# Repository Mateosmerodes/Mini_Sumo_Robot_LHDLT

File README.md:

# Mini_Sumo_Robot_LHDLT
Repositorio de informacion y código proyecto minisumo

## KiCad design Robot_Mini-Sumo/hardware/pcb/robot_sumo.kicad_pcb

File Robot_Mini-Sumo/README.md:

# 🍺 Robot Mini-Sumo · Hombres de las Tabernas

Robot mini-sumo autónomo (10 × 10 cm, < 500 g) para **Tecnología Eléctrica**, Grado en Robótica (USC), 2.ª edición. Compite según el reglamento **OSHWDem Mini Sumo rev. 7**.

**Equipo:** Mateo Esmerodes Rodríguez · Paulo Bouza García · Mario Costoya Mera

## Concepto

Rampa (cuña) clásica, **tracción 4WD** con 4 N20, una **ESP32-S3-DevKitC-1 enchufada** sobre una **PCB propia que es también el chasis**, 6 sensores ToF para encontrar al rival, 4 de línea y arranque por IR (RC5).

## Documentación

| Doc | Contenido | Estado |
|---|---|---|
| [00 · Requisitos y reglamento](docs/00-Requisitos-y-reglamento.md) | Lo que obliga al diseño | ✅ |
| [01 · Selección de componentes](docs/01-Seleccion-de-componentes.md) | Qué pieza y por qué | ✅ borrador |
| [02 · Arquitectura eléctrica](docs/02-Arquitectura-electrica.md) | Alimentación, interconexión, pinout | ✅ borrador |
| [03 · Disposición mecánica y 3D](docs/03-Disposicion-mecanica.md) | Piezas, niveles, masas, montaje, impresión | ✅ borrador |
| [04 · ESP32-S3-DevKitC-1](docs/04-ESP32-DevKitC-1.md) | Cambio a DevKit enchufable: montaje, alimentación, pinout, rutado | ✅ borrador |
| 05 · Diseño de la PCB | Esquemático ✅, colocación v1.1 ✅, ERC/DRC en KiCad 10 ⏳, rutado ⏳ | 🟡 |
| 06 · Lista de compra | AliExpress + LCSC/JLC | ⏳ |
| 07 · Costes | Desglose para el informe | ⏳ |
| Informe final | 6 páginas | ⏳ |
| [📝 Ficha técnica](docs/Ficha-tecnica.md) | Respuestas a la ficha de la competición, con los cálculos (consumo, autonomía, corrientes) | ✅ |
| [📊 Consumos y cálculos](docs/Informe-consumos-y-calculos.md) | Pieza a pieza con fuentes oficiales; cálculos de batería, motores, potencia, autonomía y señales (`hardware/calculos/`) | ✅ |
| [📋 Informe de progreso 06/10/2026](docs/Informe-progreso-2026-10-06.md) | Resumen para el equipo: proceso, compra, útiles, problemas | ✅ |

## Estructura

```
docs/                   Documentación (también es una bóveda de Obsidian)
hardware/geometria.py   Parámetros mecánicos compartidos (PCB + 3D)
hardware/generar_todo.sh  Regenera PCB, 3D, STL/STEP e imágenes
hardware/pcb/           Proyecto KiCad (scripts/design.py = circuito)
hardware/mecanica/cad/  Modelo 3D paramétrico (FreeCAD) y renderizador
hardware/mecanica/step/ Exportaciones STEP (Onshape/FreeCAD)
hardware/mecanica/stl/  Piezas listas para imprimir
firmware/               Código del ESP32-S3 (Arduino/PlatformIO; pines en docs/04)
media/fotos/            Fotos del proceso
informe/                Informe de entrega
```

## Herramientas (Linux)

```bash
sudo pacman -S --needed kicad kicad-library freecad
```

Opcional, para exportar la PCB a 3D con todos los componentes (~5 GB):

```bash
sudo pacman -S --needed kicad-library-3d
```

Licencias: hardware **CERN-OHL-S v2**, software **MIT**.

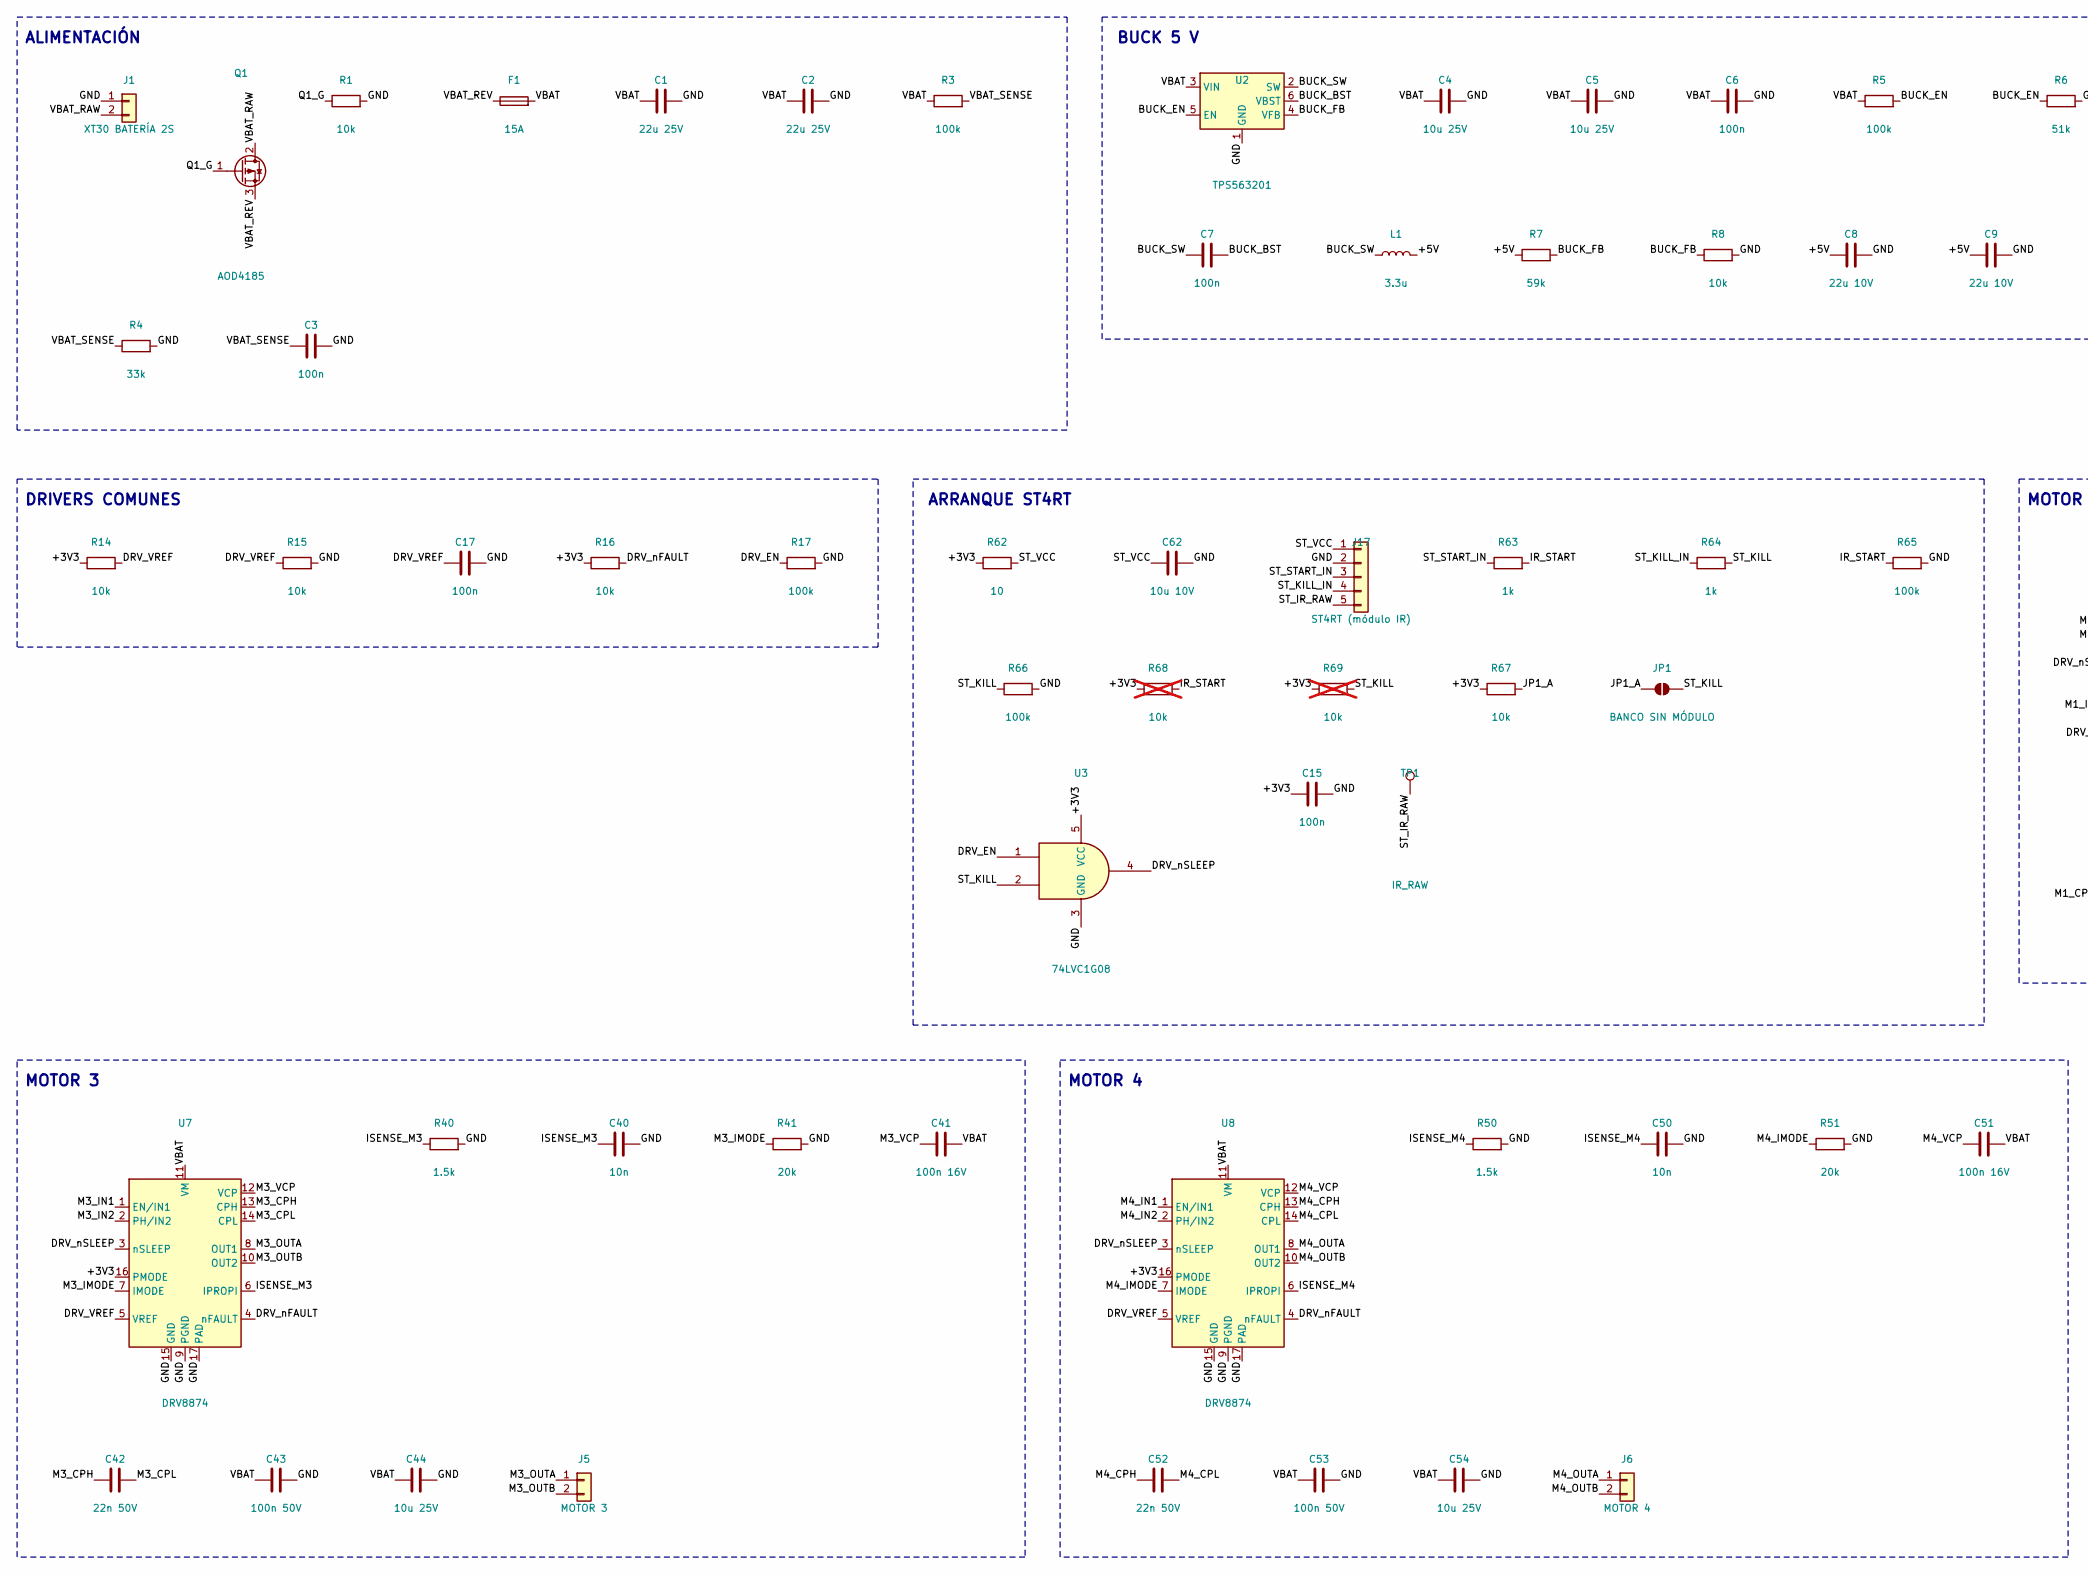
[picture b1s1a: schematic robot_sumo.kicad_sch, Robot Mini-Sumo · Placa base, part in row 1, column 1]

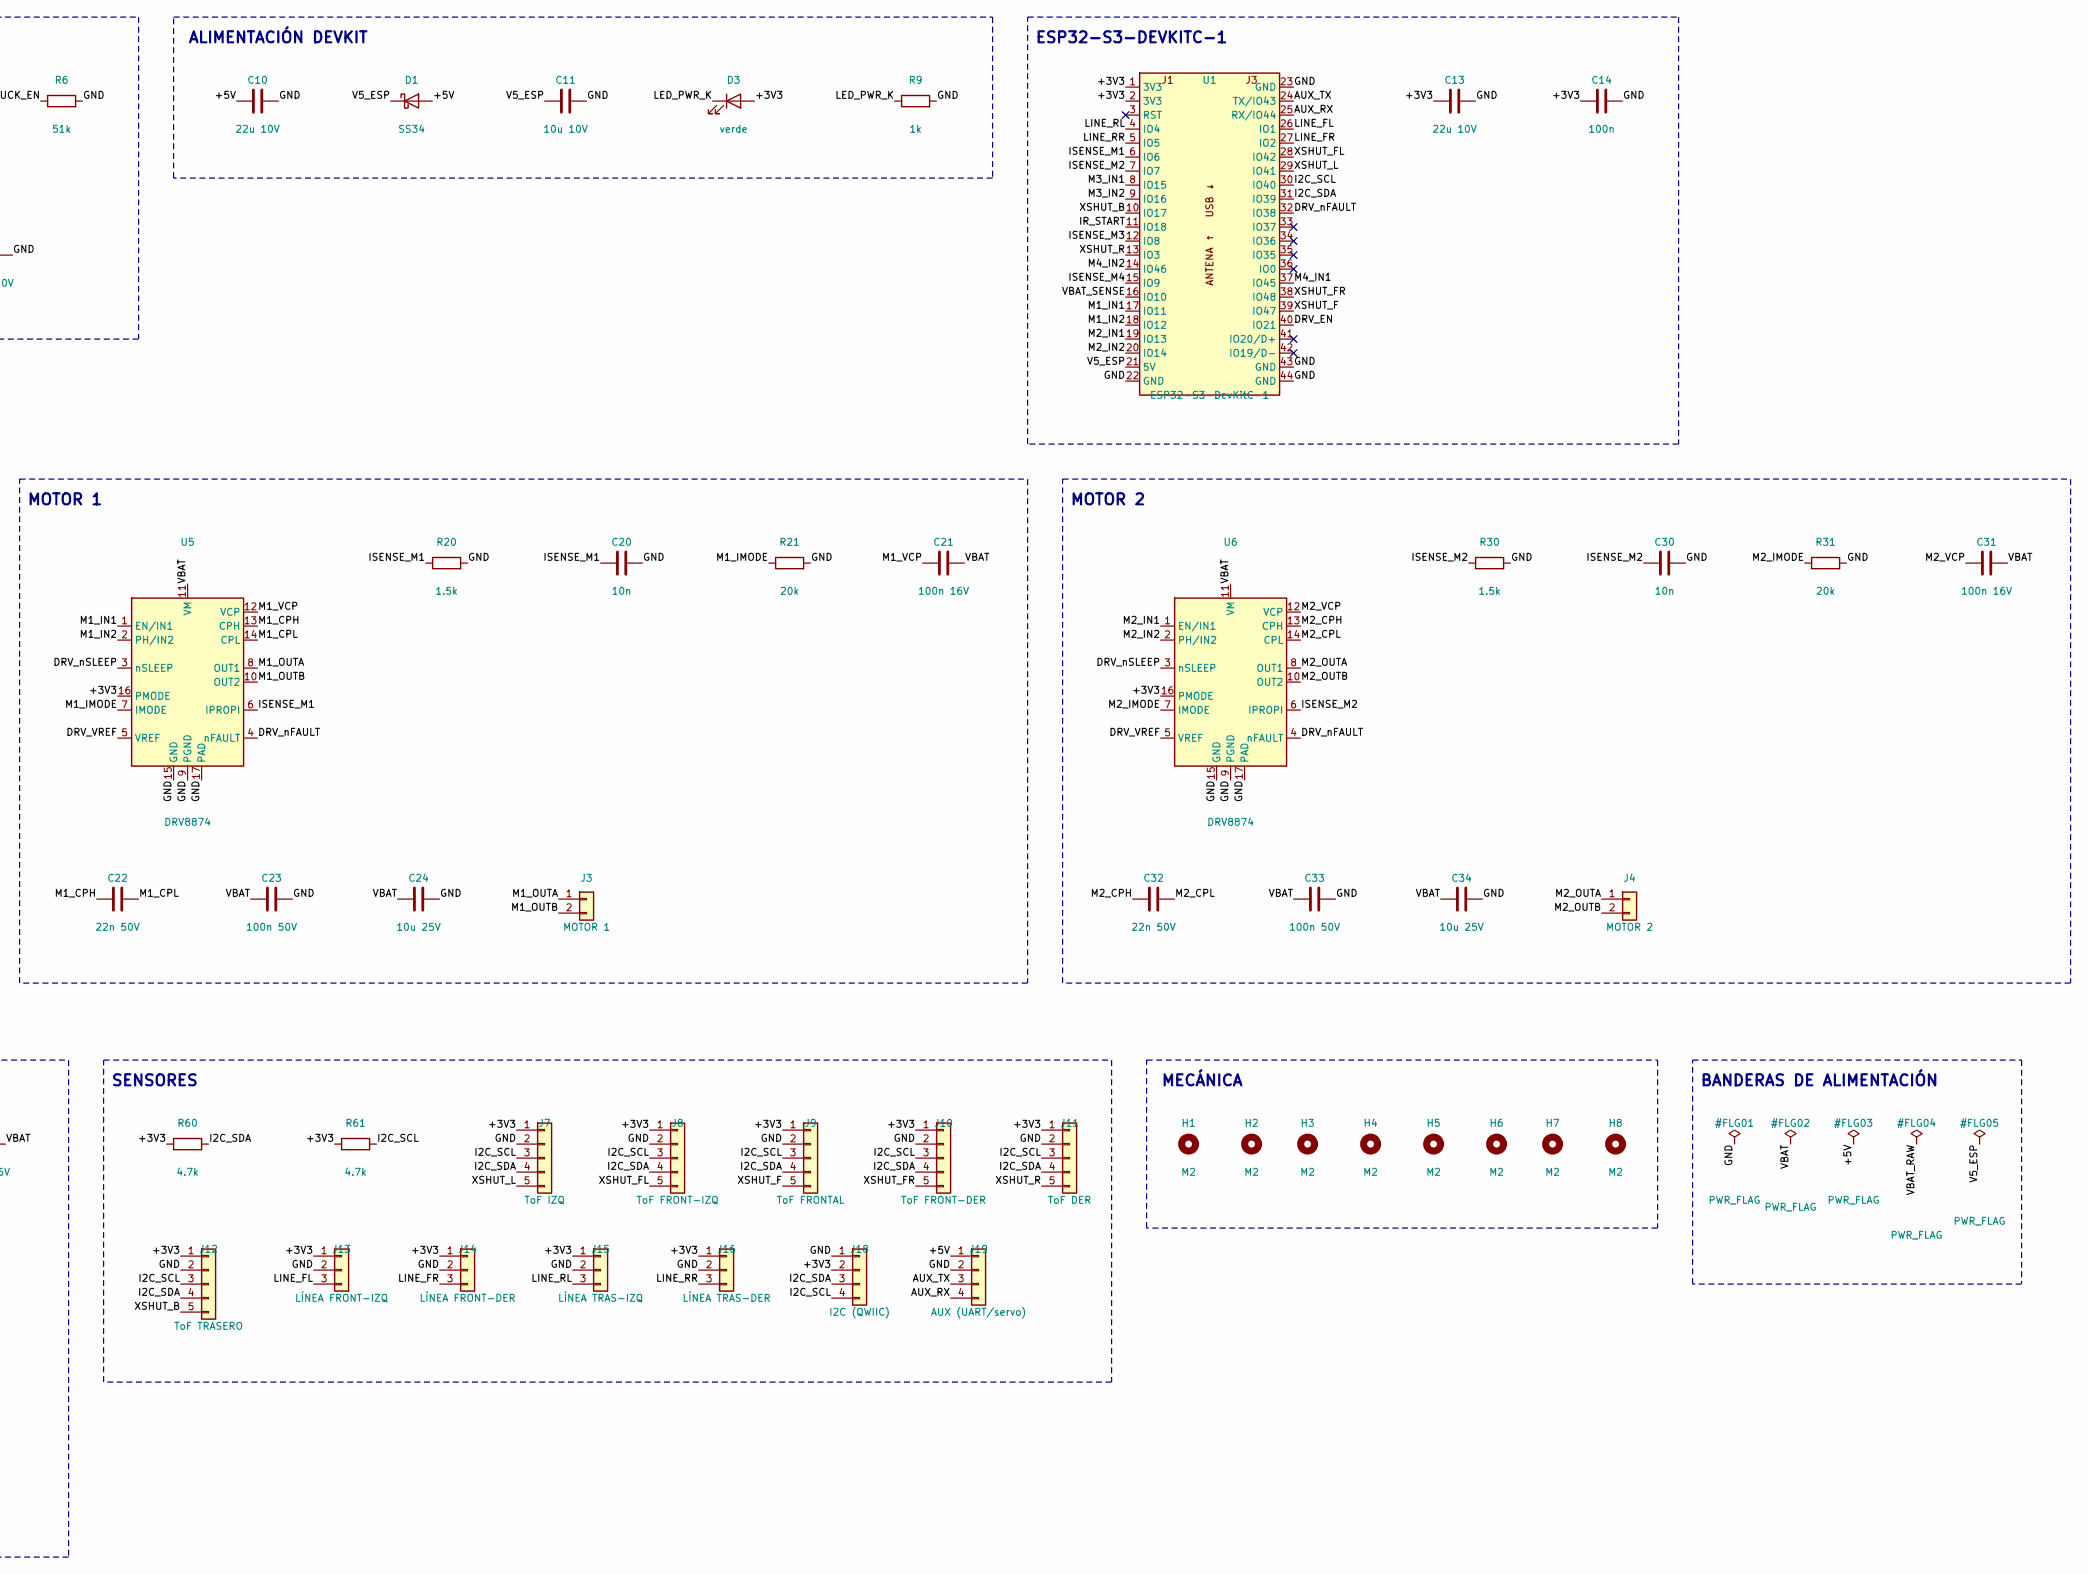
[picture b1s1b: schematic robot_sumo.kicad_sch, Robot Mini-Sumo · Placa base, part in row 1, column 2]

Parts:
C1, C2: 22u 25V; C_1206_3216Metric
C3, C6, C7, C14, C15, C17: 100n; C_0603_1608Metric
C4, C5, C24, C34, C44, C54: 10u 25V; C_1206_3216Metric
C8, C9, C10, C13: 22u 10V; C_1206_3216Metric
C11, C62: 10u 10V; C_0805_2012Metric
C20, C30, C40, C50: 10n; C_0603_1608Metric
C21, C31, C41, C51: 100n 16V; C_0402_1005Metric
C22, C32, C42, C52: 22n 50V; C_0402_1005Metric
C23, C33, C43, C53: 100n 50V; C_0603_1608Metric
D1: SS34; D_SMA
D3: verde; LED_0603_1608Metric
F1: 15A; Fuse_Littelfuse-NANO2-451_453; MPN Littelfuse NANO2 451/453, 15 A rápido (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
H1, H2, H3, H4, H5, H6, H7, H8: M2; MountingHole_2.2mm_M2
J1: XT30 BATERÍA 2S; AMASS_XT30UPB-M_1x02_P5.0mm_Vertical; MPN AMASS XT30UPB-M (macho, vertical PCB)
J3: MOTOR 1; SolderWire-0.5sqmm_1x02_P4.6mm_D0.9mm_OD2.1mm; MPN Cable del motor soldado (entra por abaj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
J4: MOTOR 2; SolderWire-0.5sqmm_1x02_P4.6mm_D0.9mm_OD2.1mm; MPN Cable del motor soldado (entra por abaj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
J5: MOTOR 3; SolderWire-0.5sqmm_1x02_P4.6mm_D0.9mm_OD2.1mm; MPN Cable del motor soldado (entra por abaj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
J6: MOTOR 4; SolderWire-0.5sqmm_1x02_P4.6mm_D0.9mm_OD2.1mm; MPN Cable del motor soldado (entra por abaj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
J7: ToF IZQ; JST_SH_BM05B-SRSS-TB_1x05-1MP_P1.00mm_Vertical; MPN JST SH 5P SMD vertical (BM05B-SRSS-TB)
J8: ToF FRONT-IZQ; JST_SH_BM05B-SRSS-TB_1x05-1MP_P1.00mm_Vertical; MPN JST SH 5P SMD vertical (BM05B-SRSS-TB)
J9: ToF FRONTAL; JST_SH_BM05B-SRSS-TB_1x05-1MP_P1.00mm_Vertical; MPN JST SH 5P SMD vertical (BM05B-SRSS-TB)
J10: ToF FRONT-DER; JST_SH_BM05B-SRSS-TB_1x05-1MP_P1.00mm_Vertical; MPN JST SH 5P SMD vertical (BM05B-SRSS-TB)
J11: ToF DER; JST_SH_BM05B-SRSS-TB_1x05-1MP_P1.00mm_Vertical; MPN JST SH 5P SMD vertical (BM05B-SRSS-TB)
J12: ToF TRASERO; JST_SH_BM05B-SRSS-TB_1x05-1MP_P1.00mm_Vertical; MPN JST SH 5P SMD vertical (BM05B-SRSS-TB)
J13: LÍNEA FRONT-IZQ; JST_SH_BM03B-SRSS-TB_1x03-1MP_P1.00mm_Vertical; MPN JST SH 3P SMD vertical (BM03B-SRSS-TB)
J14: LÍNEA FRONT-DER; JST_SH_BM03B-SRSS-TB_1x03-1MP_P1.00mm_Vertical; MPN JST SH 3P SMD vertical (BM03B-SRSS-TB)
J15: LÍNEA TRAS-IZQ; JST_SH_BM03B-SRSS-TB_1x03-1MP_P1.00mm_Vertical; MPN JST SH 3P SMD vertical (BM03B-SRSS-TB)
J16: LÍNEA TRAS-DER; JST_SH_BM03B-SRSS-TB_1x03-1MP_P1.00mm_Vertical; MPN JST SH 3P SMD vertical (BM03B-SRSS-TB)
J17: ST4RT (módulo IR); JST_SH_BM05B-SRSS-TB_1x05-1MP_P1.00mm_Vertical; MPN JST SH 5P SMD vertical (BM05B-SRSS-TB) 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
J18: I2C (QWIIC); JST_SH_BM04B-SRSS-TB_1x04-1MP_P1.00mm_Vertical; MPN JST SH 4P SMD vertical (BM04B-SRSS-TB)
J19: AUX (UART/servo); JST_SH_BM04B-SRSS-TB_1x04-1MP_P1.00mm_Vertical; MPN JST SH 4P SMD vertical (BM04B-SRSS-TB)
JP1: BANCO SIN MÓDULO; SolderJumper-2_P1.3mm_Open_RoundedPad1.0x1.5mm; MPN Puente de soldadura: cerrado = KILL a 1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
L1: 3.3u; L_Bourns-SRN4018; MPN SRN4018-3R3M (3,3 µH, Isat ≥ 2,5 A)
Q1: AOD4185; TO-252-2; MPN AOD4185 (-40 V, -40 A, 15 mΩ)
R1, R8, R14, R15, R16, R67: 10k; R_0603_1608Metric
R3, R5, R17, R65, R66: 100k; R_0603_1608Metric
R4: 33k; R_0603_1608Metric
R6: 51k; R_0603_1608Metric
R7: 59k; R_0603_1608Metric
R9, R63, R64: 1k; R_0603_1608Metric
R20, R30, R40, R50: 1.5k; R_0603_1608Metric
R21, R31, R41, R51: 20k; R_0603_1608Metric
R60, R61: 4.7k; R_0603_1608Metric
R62: 10; R_0603_1608Metric
R68: 10k; R_0603_1608Metric; MPN DNP: solo si S es de drenador abierto; not fitted
R69: 10k; R_0603_1608Metric; MPN DNP: solo si K es de drenador abierto; not fitted
TP1: IR_RAW; TestPoint_Pad_D1.0mm; MPN Punto de prueba (salida IR en bruto del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
U1: ESP32-S3-DevKitC-1; ESP32-S3-DevKitC-1_Zocalo; MPN ESP32-S3-DevKitC-1 (cualquier variante: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
U2: TPS563201; SOT-23-6; MPN TPS563201DDCR
U3: 74LVC1G08; SOT-23-5; MPN SN74LVC1G08DBVR
U5, U6, U7, U8: DRV8874; HTSSOP-16-1EP_4.4x5mm_P0.65mm_EP3.4x5mm_Mask2.46x2.31mm; MPN DRV8874PWPR

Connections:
+3V3: C13.1, C14.1, C15.1, D3.2 (A), J7.1, J8.1, J9.1, J10.1, J11.1, J12.1, J13.1, J14.1, J15.1, J16.1, J18.2, R14.1, R16.1, R60.1, R61.1, R62.1, R67.1, R68.1, R69.1, U1.1 (3V3), U1.2 (3V3), U3.5 (VCC), U5.16 (PMODE), U6.16 (PMODE), U7.16 (PMODE), U8.16 (PMODE)
+5V: C8.1, C9.1, C10.1, D1.2 (A), J19.1, L1.2, R7.1
AUX_RX: J19.4, U1.25 (RX/IO44)
AUX_TX: J19.3, U1.24 (TX/IO43)
BUCK_BST: C7.2, U2.6 (VBST)
BUCK_EN: R5.2, R6.1, U2.5 (EN)
BUCK_FB: R7.2, R8.1, U2.4 (VFB)
BUCK_SW: C7.1, L1.1, U2.2 (SW)
DRV_EN: R17.1, U1.40 (IO21), U3.1
DRV_VREF: C17.1, R14.2, R15.1, U5.5 (VREF), U6.5 (VREF), U7.5 (VREF), U8.5 (VREF)
DRV_nFAULT: R16.2, U1.32 (IO38), U5.4 (nFAULT), U6.4 (nFAULT), U7.4 (nFAULT), U8.4 (nFAULT)
DRV_nSLEEP: U3.4, U5.3 (nSLEEP), U6.3 (nSLEEP), U7.3 (nSLEEP), U8.3 (nSLEEP)
GND: C1.2, C2.2, C3.2, C4.2, C5.2, C6.2, C8.2, C9.2, C10.2, C11.2, C13.2, C14.2, C15.2, C17.2, C20.2, C23.2, C24.2, C30.2, C33.2, C34.2, C40.2, C43.2, C44.2, C50.2, C53.2, C54.2, C62.2, J1.1, J7.2, J8.2, J9.2, J10.2, J11.2, J12.2, J13.2, J14.2, J15.2, J16.2, J17.2, J18.1, J19.2, R1.2, R4.2, R6.2, R8.2, R9.2, R15.2, R17.2, R20.2, R21.2, R30.2, R31.2, R40.2, R41.2, R50.2, R51.2, R65.2, R66.2, U1.22 (GND), U1.23 (GND), U1.43 (GND), U1.44 (GND), U2.1 (GND), U3.3 (GND), U5.9 (PGND), U5.15 (GND), U5.17 (PAD), U6.9 (PGND), U6.15 (GND), U6.17 (PAD), U7.9 (PGND), U7.15 (GND), U7.17 (PAD), U8.9 (PGND), U8.15 (GND), U8.17 (PAD)
I2C_SCL: J7.3, J8.3, J9.3, J10.3, J11.3, J12.3, J18.4, R61.2, U1.30 (IO40)
I2C_SDA: J7.4, J8.4, J9.4, J10.4, J11.4, J12.4, J18.3, R60.2, U1.31 (IO39)
IR_START: R63.2, R65.1, R68.2, U1.11 (IO18)
ISENSE_M1: C20.1, R20.1, U1.6 (IO6), U5.6 (IPROPI)
ISENSE_M2: C30.1, R30.1, U1.7 (IO7), U6.6 (IPROPI)
ISENSE_M3: C40.1, R40.1, U1.12 (IO8), U7.6 (IPROPI)
ISENSE_M4: C50.1, R50.1, U1.15 (IO9), U8.6 (IPROPI)
JP1_A: JP1.1 (A), R67.2
LED_PWR_K: D3.1 (K), R9.1
LINE_FL: J13.3, U1.26 (IO1)
LINE_FR: J14.3, U1.27 (IO2)
LINE_RL: J15.3, U1.4 (IO4)
LINE_RR: J16.3, U1.5 (IO5)
M1_CPH: C22.1, U5.13 (CPH)
M1_CPL: C22.2, U5.14 (CPL)
M1_IMODE: R21.1, U5.7 (IMODE)
M1_IN1: U1.17 (IO11), U5.1 (EN/IN1)
M1_IN2: U1.18 (IO12), U5.2 (PH/IN2)
M1_OUTA: J3.1, U5.8 (OUT1)
M1_OUTB: J3.2, U5.10 (OUT2)
M1_VCP: C21.1, U5.12 (VCP)
M2_CPH: C32.1, U6.13 (CPH)
M2_CPL: C32.2, U6.14 (CPL)
M2_IMODE: R31.1, U6.7 (IMODE)
M2_IN1: U1.19 (IO13), U6.1 (EN/IN1)
M2_IN2: U1.20 (IO14), U6.2 (PH/IN2)
M2_OUTA: J4.1, U6.8 (OUT1)
M2_OUTB: J4.2, U6.10 (OUT2)
M2_VCP: C31.1, U6.12 (VCP)
M3_CPH: C42.1, U7.13 (CPH)
M3_CPL: C42.2, U7.14 (CPL)
M3_IMODE: R41.1, U7.7 (IMODE)
M3_IN1: U1.8 (IO15), U7.1 (EN/IN1)
M3_IN2: U1.9 (IO16), U7.2 (PH/IN2)
M3_OUTA: J5.1, U7.8 (OUT1)
M3_OUTB: J5.2, U7.10 (OUT2)
M3_VCP: C41.1, U7.12 (VCP)
M4_CPH: C52.1, U8.13 (CPH)
M4_CPL: C52.2, U8.14 (CPL)
M4_IMODE: R51.1, U8.7 (IMODE)
M4_IN1: U1.37 (IO45), U8.1 (EN/IN1)
M4_IN2: U1.14 (IO46), U8.2 (PH/IN2)
M4_OUTA: J6.1, U8.8 (OUT1)
M4_OUTB: J6.2, U8.10 (OUT2)
M4_VCP: C51.1, U8.12 (VCP)
Q1_G: Q1.1 (G), R1.1
ST_IR_RAW: J17.5, TP1.1
ST_KILL: JP1.2 (B), R64.2, R66.1, R69.2, U3.2
ST_KILL_IN: J17.4, R64.1
ST_START_IN: J17.3, R63.1
ST_VCC: C62.1, J17.1, R62.2
V5_ESP: C11.1, D1.1 (K), U1.21 (5V)
VBAT: C1.1, C2.1, C4.1, C5.1, C6.1, C21.2, C23.1, C24.1, C31.2, C33.1, C34.1, C41.2, C43.1, C44.1, C51.2, C53.1, C54.1, F1.2, R3.1, R5.1, U2.3 (VIN), U5.11 (VM), U6.11 (VM), U7.11 (VM), U8.11 (VM)
VBAT_RAW: J1.2, Q1.2 (D)
VBAT_REV: F1.1, Q1.3 (S)
VBAT_SENSE: C3.1, R3.2, R4.1, U1.16 (IO10)
XSHUT_B: J12.5, U1.10 (IO17)
XSHUT_F: J9.5, U1.39 (IO47)
XSHUT_FL: J8.5, U1.28 (IO42)
XSHUT_FR: J10.5, U1.38 (IO48)
XSHUT_L: J7.5, U1.29 (IO41)
XSHUT_R: J11.5, U1.13 (IO3)

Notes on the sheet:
ALIMENTACIÓN
BUCK 5 V
ALIMENTACIÓN DEVKIT
ESP32-S3-DEVKITC-1
DRIVERS COMUNES
ARRANQUE ST4RT
MOTOR 1
MOTOR 2
MOTOR 3
MOTOR 4
SENSORES
MECÁNICA
BANDERAS DE ALIMENTACIÓN

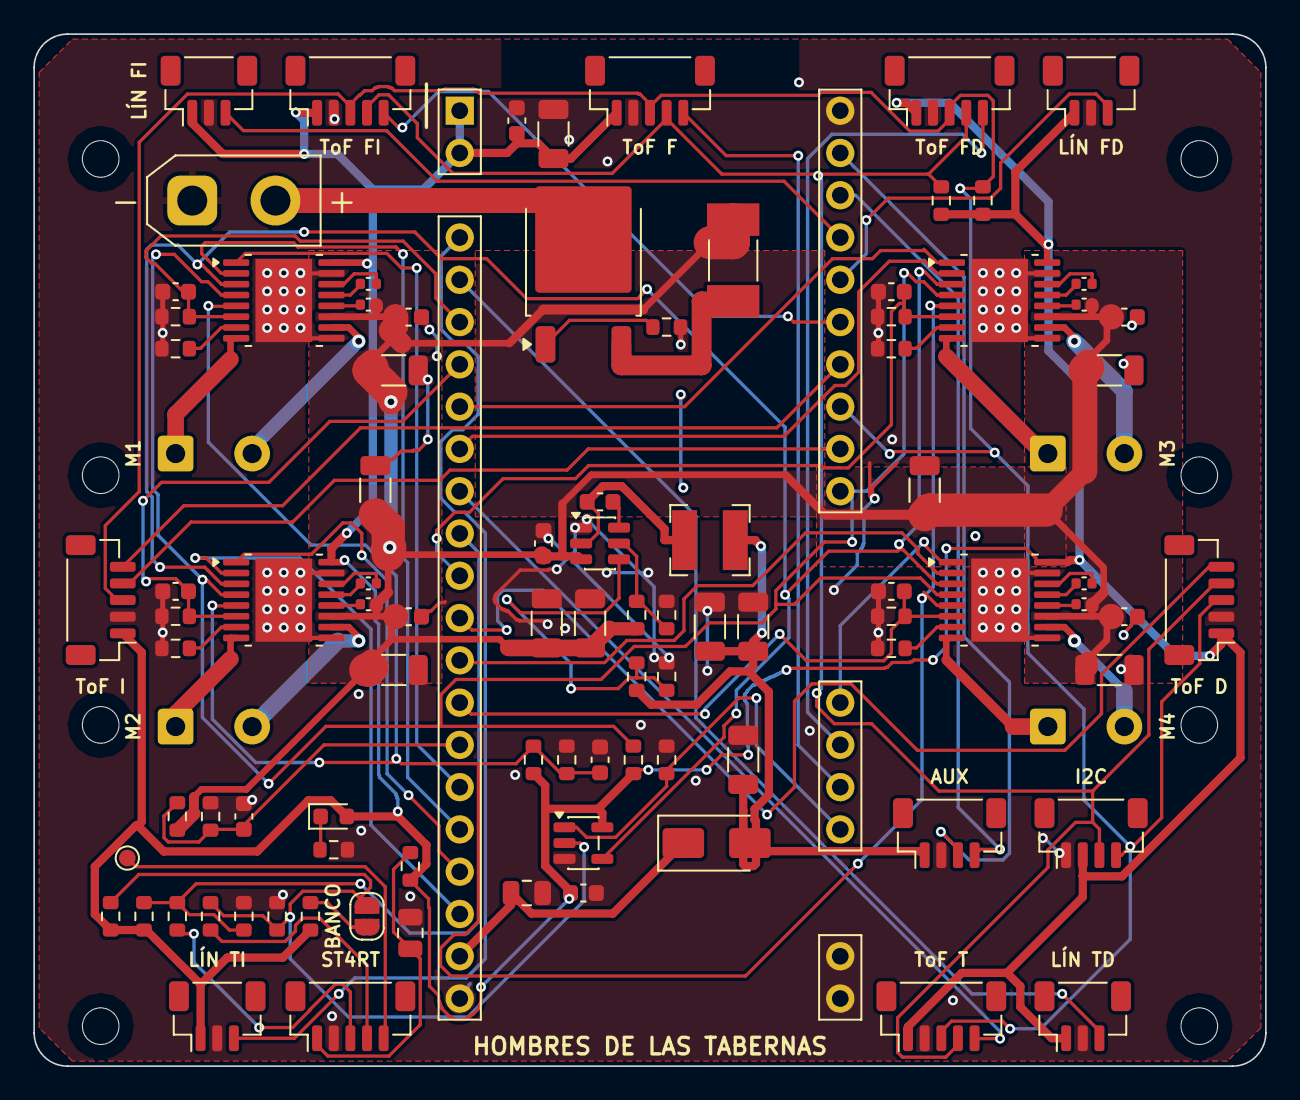
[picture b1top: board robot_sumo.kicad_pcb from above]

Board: 2 copper layers, 74.0 x 62.0 mm, 106 parts (0 on the bottom side), 75 nets.

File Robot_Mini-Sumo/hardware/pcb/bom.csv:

Comment,Designator,Footprint,LCSC,MPN,Cantidad
22u 25V,"C1,C2",C_1206_3216Metric,,,2
100n,"C3,C6,C7,C14,C15,C17",C_0603_1608Metric,,,6
10u 25V,"C4,C5,C24,C34,C44,C54",C_1206_3216Metric,,,6
22u 10V,"C8,C9,C10,C13",C_1206_3216Metric,,,4
10u 10V,"C11,C62",C_0805_2012Metric,,,2
10n,"C20,C30,C40,C50",C_0603_1608Metric,,,4
100n 16V,"C21,C31,C41,C51",C_0603_1608Metric,,,4
22n 50V,"C22,C32,C42,C52",C_0603_1608Metric,,,4
100n 50V,"C23,C33,C43,C53",C_0603_1608Metric,,,4
SS34,D1,D_SMA,,,1
verde,D3,LED_0603_1608Metric,,,1
15A,F1,Fuse_Littelfuse-NANO2-451_453,,"Littelfuse NANO2 451/453, 15 A rápido (p. ej. 0451015.MRL; verificar stock)",1
XT30 BATERÍA 2S,J1,AMASS_XT30UPB-M_1x02_P5.0mm_Vertical,,"AMASS XT30UPB-M (macho, vertical PCB)",1
MOTOR 1,J3,SolderWire-0.5sqmm_1x02_P4.6mm_D0.9mm_OD2.1mm,,Cable del motor soldado (entra por abajo),1
MOTOR 2,J4,SolderWire-0.5sqmm_1x02_P4.6mm_D0.9mm_OD2.1mm,,Cable del motor soldado (entra por abajo),1
MOTOR 3,J5,SolderWire-0.5sqmm_1x02_P4.6mm_D0.9mm_OD2.1mm,,Cable del motor soldado (entra por abajo),1
MOTOR 4,J6,SolderWire-0.5sqmm_1x02_P4.6mm_D0.9mm_OD2.1mm,,Cable del motor soldado (entra por abajo),1
ToF IZQ,J7,JST_SH_BM05B-SRSS-TB_1x05-1MP_P1.00mm_Vertical,,JST SH 5P SMD vertical (BM05B-SRSS-TB),1
ToF FRONT-IZQ,J8,JST_SH_BM05B-SRSS-TB_1x05-1MP_P1.00mm_Vertical,,JST SH 5P SMD vertical (BM05B-SRSS-TB),1
ToF FRONTAL,J9,JST_SH_BM05B-SRSS-TB_1x05-1MP_P1.00mm_Vertical,,JST SH 5P SMD vertical (BM05B-SRSS-TB),1
ToF FRONT-DER,J10,JST_SH_BM05B-SRSS-TB_1x05-1MP_P1.00mm_Vertical,,JST SH 5P SMD vertical (BM05B-SRSS-TB),1
ToF DER,J11,JST_SH_BM05B-SRSS-TB_1x05-1MP_P1.00mm_Vertical,,JST SH 5P SMD vertical (BM05B-SRSS-TB),1
ToF TRASERO,J12,JST_SH_BM05B-SRSS-TB_1x05-1MP_P1.00mm_Vertical,,JST SH 5P SMD vertical (BM05B-SRSS-TB),1
LÍNEA FRONT-IZQ,J13,JST_SH_BM03B-SRSS-TB_1x03-1MP_P1.00mm_Vertical,,JST SH 3P SMD vertical (BM03B-SRSS-TB),1
LÍNEA FRONT-DER,J14,JST_SH_BM03B-SRSS-TB_1x03-1MP_P1.00mm_Vertical,,JST SH 3P SMD vertical (BM03B-SRSS-TB),1
LÍNEA TRAS-IZQ,J15,JST_SH_BM03B-SRSS-TB_1x03-1MP_P1.00mm_Vertical,,JST SH 3P SMD vertical (BM03B-SRSS-TB),1
LÍNEA TRAS-DER,J16,JST_SH_BM03B-SRSS-TB_1x03-1MP_P1.00mm_Vertical,,JST SH 3P SMD vertical (BM03B-SRSS-TB),1
ST4RT (módulo IR),J17,JST_SH_BM05B-SRSS-TB_1x05-1MP_P1.00mm_Vertical,,JST SH 5P SMD vertical (BM05B-SRSS-TB) + cable a medida hasta el módulo,1
I2C (QWIIC),J18,JST_SH_BM04B-SRSS-TB_1x04-1MP_P1.00mm_Vertical,,JST SH 4P SMD vertical (BM04B-SRSS-TB),1
AUX (UART/servo),J19,JST_SH_BM04B-SRSS-TB_1x04-1MP_P1.00mm_Vertical,,JST SH 4P SMD vertical (BM04B-SRSS-TB),1
BANCO SIN MÓDULO,JP1,SolderJumper-2_P1.3mm_Open_RoundedPad1.0x1.5mm,,Puente de soldadura: cerrado = KILL a 1 sin módulo (solo banco),1
3.3u,L1,L_Bourns-SRN4018,,"SRN4018-3R3M (3,3 µH, Isat ≥ 2,5 A)",1
AOD4185,Q1,TO-252-2,,"AOD4185 (-40 V, -40 A, 15 mΩ)",1
10k,"R1,R8,R14,R15,R16,R67",R_0603_1608Metric,,,6
100k,"R3,R5,R17,R65,R66",R_0603_1608Metric,,,5
33k,R4,R_0603_1608Metric,,,1
51k,R6,R_0603_1608Metric,,,1
59k,R7,R_0603_1608Metric,,,1
1k,"R9,R63,R64",R_0603_1608Metric,,,3
1.5k,"R20,R30,R40,R50",R_0603_1608Metric,,,4
20k,"R21,R31,R41,R51",R_0603_1608Metric,,,4
4.7k,"R60,R61",R_0603_1608Metric,,,2
10,R62,R_0603_1608Metric,,,1
IR_RAW,TP1,TestPoint_Pad_D1.0mm,,"Punto de prueba (salida IR en bruto del módulo, sin uso en combate)",1
ESP32-S3-DevKitC-1,U1,ESP32-S3-DevKitC-1_Zocalo,,"ESP32-S3-DevKitC-1 (cualquier variante: N8, N8R2, N8R8, N16R8) + tiras hembra 2,54 mm cortadas",1
TPS563201,U2,SOT-23-6,,TPS563201DDCR,1
74LVC1G08,U3,SOT-23-5,,SN74LVC1G08DBVR,1
DRV8874,"U5,U6,U7,U8",HTSSOP-16-1EP_4.4x5mm_P0.65mm_EP3.4x5mm_Mask2.46x2.31mm,,DRV8874PWPR,4

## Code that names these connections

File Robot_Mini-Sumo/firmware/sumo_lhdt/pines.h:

// pines.h — ESP32-S3-DevKitC-1 sobre la placa base v1.2 (HOMBRES DE LAS TABERNAS)
// Fuente única: hardware/pcb/scripts/design.py. Si cambia allí, cambia aquí.
#pragma once

namespace pin {
// Sensores de línea QRE1113 (ADC1)
constexpr int LINE_FL = 1, LINE_FR = 2, LINE_RL = 4, LINE_RR = 5;
// IPROPI de los DRV8874 (ADC1): V = I · 455 µA/A · 1,5 kΩ
constexpr int ISENSE_M1 = 6, ISENSE_M2 = 7, ISENSE_M3 = 8, ISENSE_M4 = 9;
// Batería: divisor 100 k / 33 k (ADC1)
constexpr int VBAT_SENSE = 10;
// Motores (modo PWM del DRV8874). M1 izq. del., M2 izq. tras., M3 der. del., M4 der. tras.
constexpr int M1_IN1 = 11, M1_IN2 = 12, M2_IN1 = 13, M2_IN2 = 14;
constexpr int M3_IN1 = 15, M3_IN2 = 16, M4_IN1 = 45, M4_IN2 = 46;  // 45/46: pines de arranque, a 0 al encender
// DRV_EN: el firmware habilita los drivers. En la v1.2 nSLEEP = DRV_EN AND KILL (U3), así que el
// módulo de arranque puede dormirlos aunque este pin esté a 1.
constexpr int DRV_EN = 21, DRV_nFAULT = 38;
// I2C de los VL53L0X y XSHUT de cada uno
constexpr int I2C_SDA = 39, I2C_SCL = 40;
constexpr int XSHUT_L = 41, XSHUT_FL = 42, XSHUT_F = 47, XSHUT_FR = 48, XSHUT_R = 3, XSHUT_B = 17;
// Módulo de arranque ST4RT: salida S (START) a través de R63 (1 k), con R65 (100 k) a GND
constexpr int ST_START = 18;
// Botón BOOT de la DevKit (en la propia DevKit; GPIO0 no tiene zócalo en la placa base)
constexpr int BTN_USER = 0;
}  // namespace pin

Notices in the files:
Robot_Mini-Sumo/hardware/pcb/robot_sumo.kicad_pcb:
Robot Mini-Sumo v1.2 · Tecnología Eléctrica · USC · 2026 · CERN-OHL-S v2
Robot_Mini-Sumo/hardware/pcb/robot_sumo.kicad_sch:
Licencia CERN-OHL-S v2
